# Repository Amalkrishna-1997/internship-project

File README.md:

# internship-project
dual smps ciruit controlled by esp32 with 3rd power sourse as a battery
smps control these 2 smps and battery controlled relay circuit

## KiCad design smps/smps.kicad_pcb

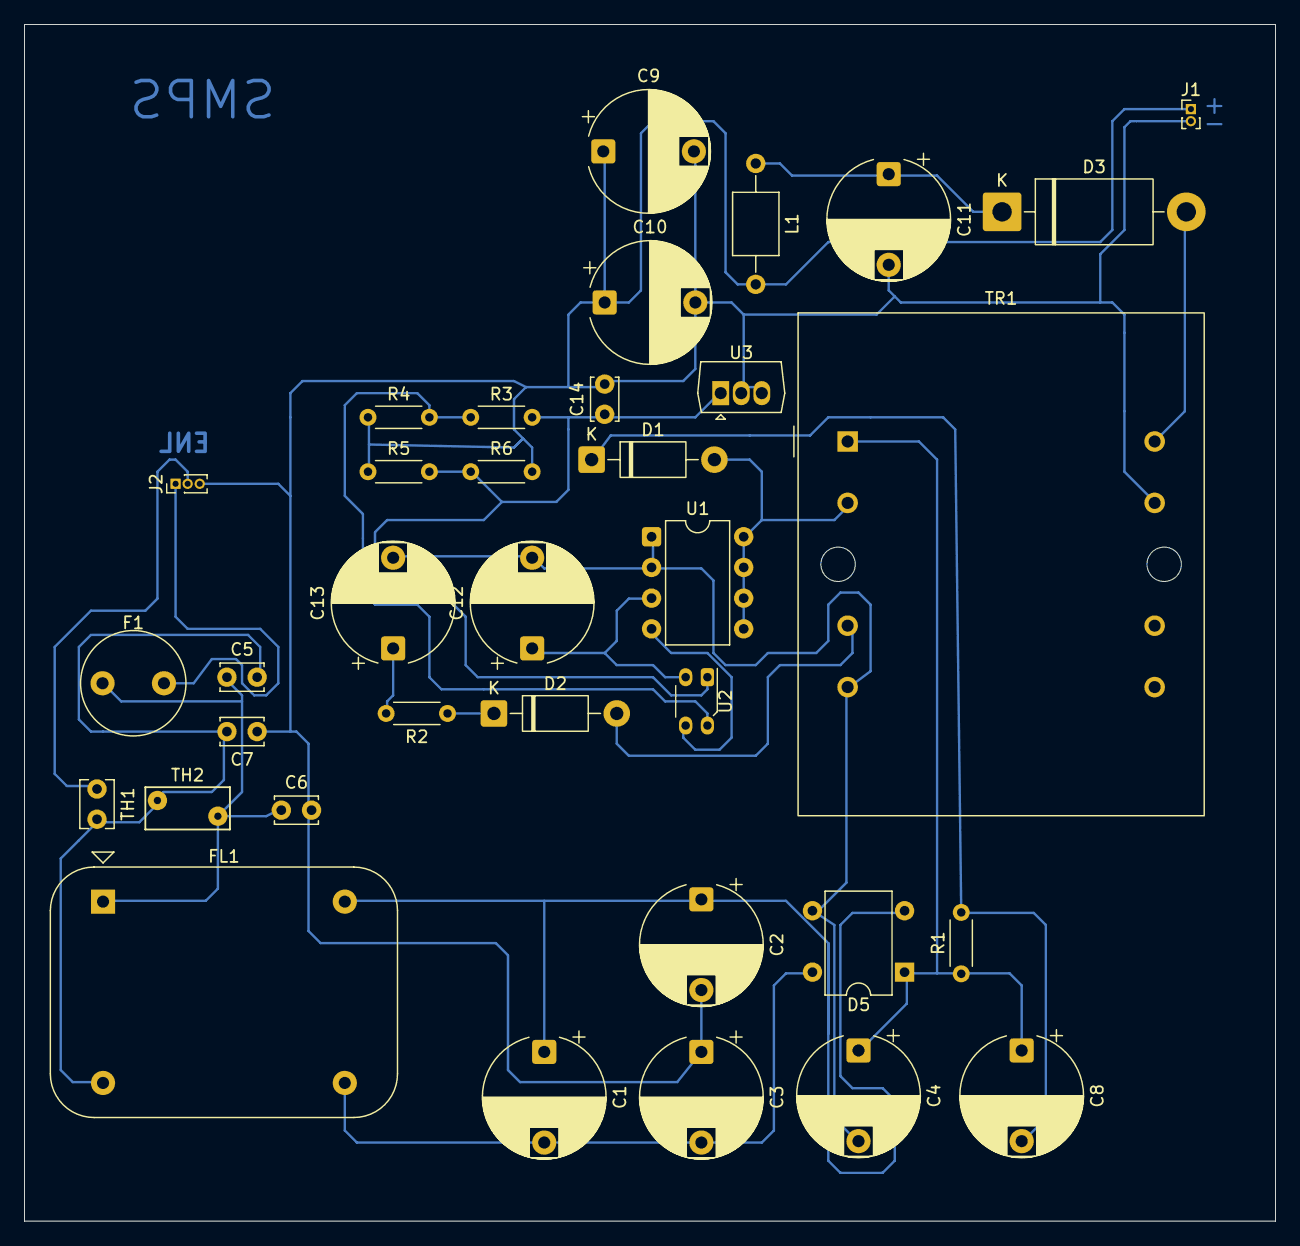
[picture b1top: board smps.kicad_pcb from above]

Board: 2 copper layers, 103.5 x 99.0 mm, 35 parts (0 on the bottom side), 21 nets, no tracks yet.

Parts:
C1, C2, C3, C8, C10, C11: C_Small; CP_Radial_D10.0mm_P7.50mm
C4, C9, C13: C_Polarized_US; CP_Radial_D10.0mm_P7.50mm
C5, C6, C7: C_Small; C_Disc_D3.4mm_W2.1mm_P2.50mm
C12: C; CP_Radial_D10.0mm_P7.50mm
C14: C; C_Disc_D3.4mm_W2.1mm_P2.50mm
D1, D2: 1N4936; D_DO-41_SOD81_P10.16mm_Horizontal
D3: 1N5822; D_DO-201AD_P15.24mm_Horizontal
D5: KBPC3501W; Diode_Bridge_DIP-4_W7.62mm_P5.08mm
F1: Fuse; Fuse_Littelfuse_372_D8.50mm
FL1: Filter_EMI_LL; Filter_FILTERCON_1FPxx
J1: Conn_01x02_Pin; PinHeader_1x02_P1.00mm_Vertical
J2: Conn_01x03_Pin; PinHeader_1x03_P1.00mm_Vertical
L1: L; L_Axial_L5.0mm_D3.6mm_P10.00mm_Horizontal_Murata_BL01RN1A2A2
R1: R_Small; R_Axial_DIN0204_L3.6mm_D1.6mm_P5.08mm_Horizontal
R2, R3, R4, R5, R6: R_Small_US; R_Axial_DIN0204_L3.6mm_D1.6mm_P5.08mm_Horizontal
TH1: Thermistor_NTC; C_Disc_D3.8mm_W2.6mm_P2.50mm
TH2: Thermistor_NTC; RV_Disc_D7mm_W3.5mm_P5mm
TR1: Triad_VPP16-310; Transformer_Triad_VPP16-310
U1: VIPer22AS; DIP-8_W7.62mm
U2: GP2S700HCP; Everlight_ITR8307F43
U3: TL431D; NEC_Molded_7x4x9mm

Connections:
Earth: C2.2, C3.1, C6.2, C7.1, C9.2, C10.2, C11.2, C14.2, J1.2, J2.3, R6.2, TR1.9, U3.2 (A), U3.3 (A)
unnamed: C1.1, C2.1, D5.2, FL1.2
unnamed: C1.2, C3.2, D5.4, FL1.4
unnamed: C5.1, C6.1, F1.1, FL1.1, TH2.1
unnamed: C5.2, C7.2, FL1.3, TH1.2, TH2.2
unnamed: C13.1, R2.2
unnamed: D1.2 (A), TR1.3, U1.5 (D), U1.6 (D), U1.7 (D), U1.8 (D)
unnamed: C8.2, D1.1 (K), R1.2
unnamed: D2.2 (A), TR1.4
unnamed: D2.1 (K), R2.1
unnamed: D3.2 (A), TR1.7
unnamed: C11.1, D3.1 (K), L1.1
unnamed: C4.1, C8.1, D5.1 (+), R1.1, TR1.1
unnamed: C4.2, C12.2, C13.2, D5.3 (-), TR1.6, U1.1 (S), U1.2 (S)
unnamed: C9.1, C10.1, J1.1, L1.2, R4.1, R5.1
unnamed: F1.2, J2.1
unnamed: J2.2, TH1.1
unnamed: R3.1, R4.2, U2.2
unnamed: C12.1, U1.3 (FB), U2.3 (K)
unnamed: U1.4 (VDD), U2.4 (A)
unnamed: C14.1, R3.2, R5.2, R6.1, U2.1, U3.1 (K)

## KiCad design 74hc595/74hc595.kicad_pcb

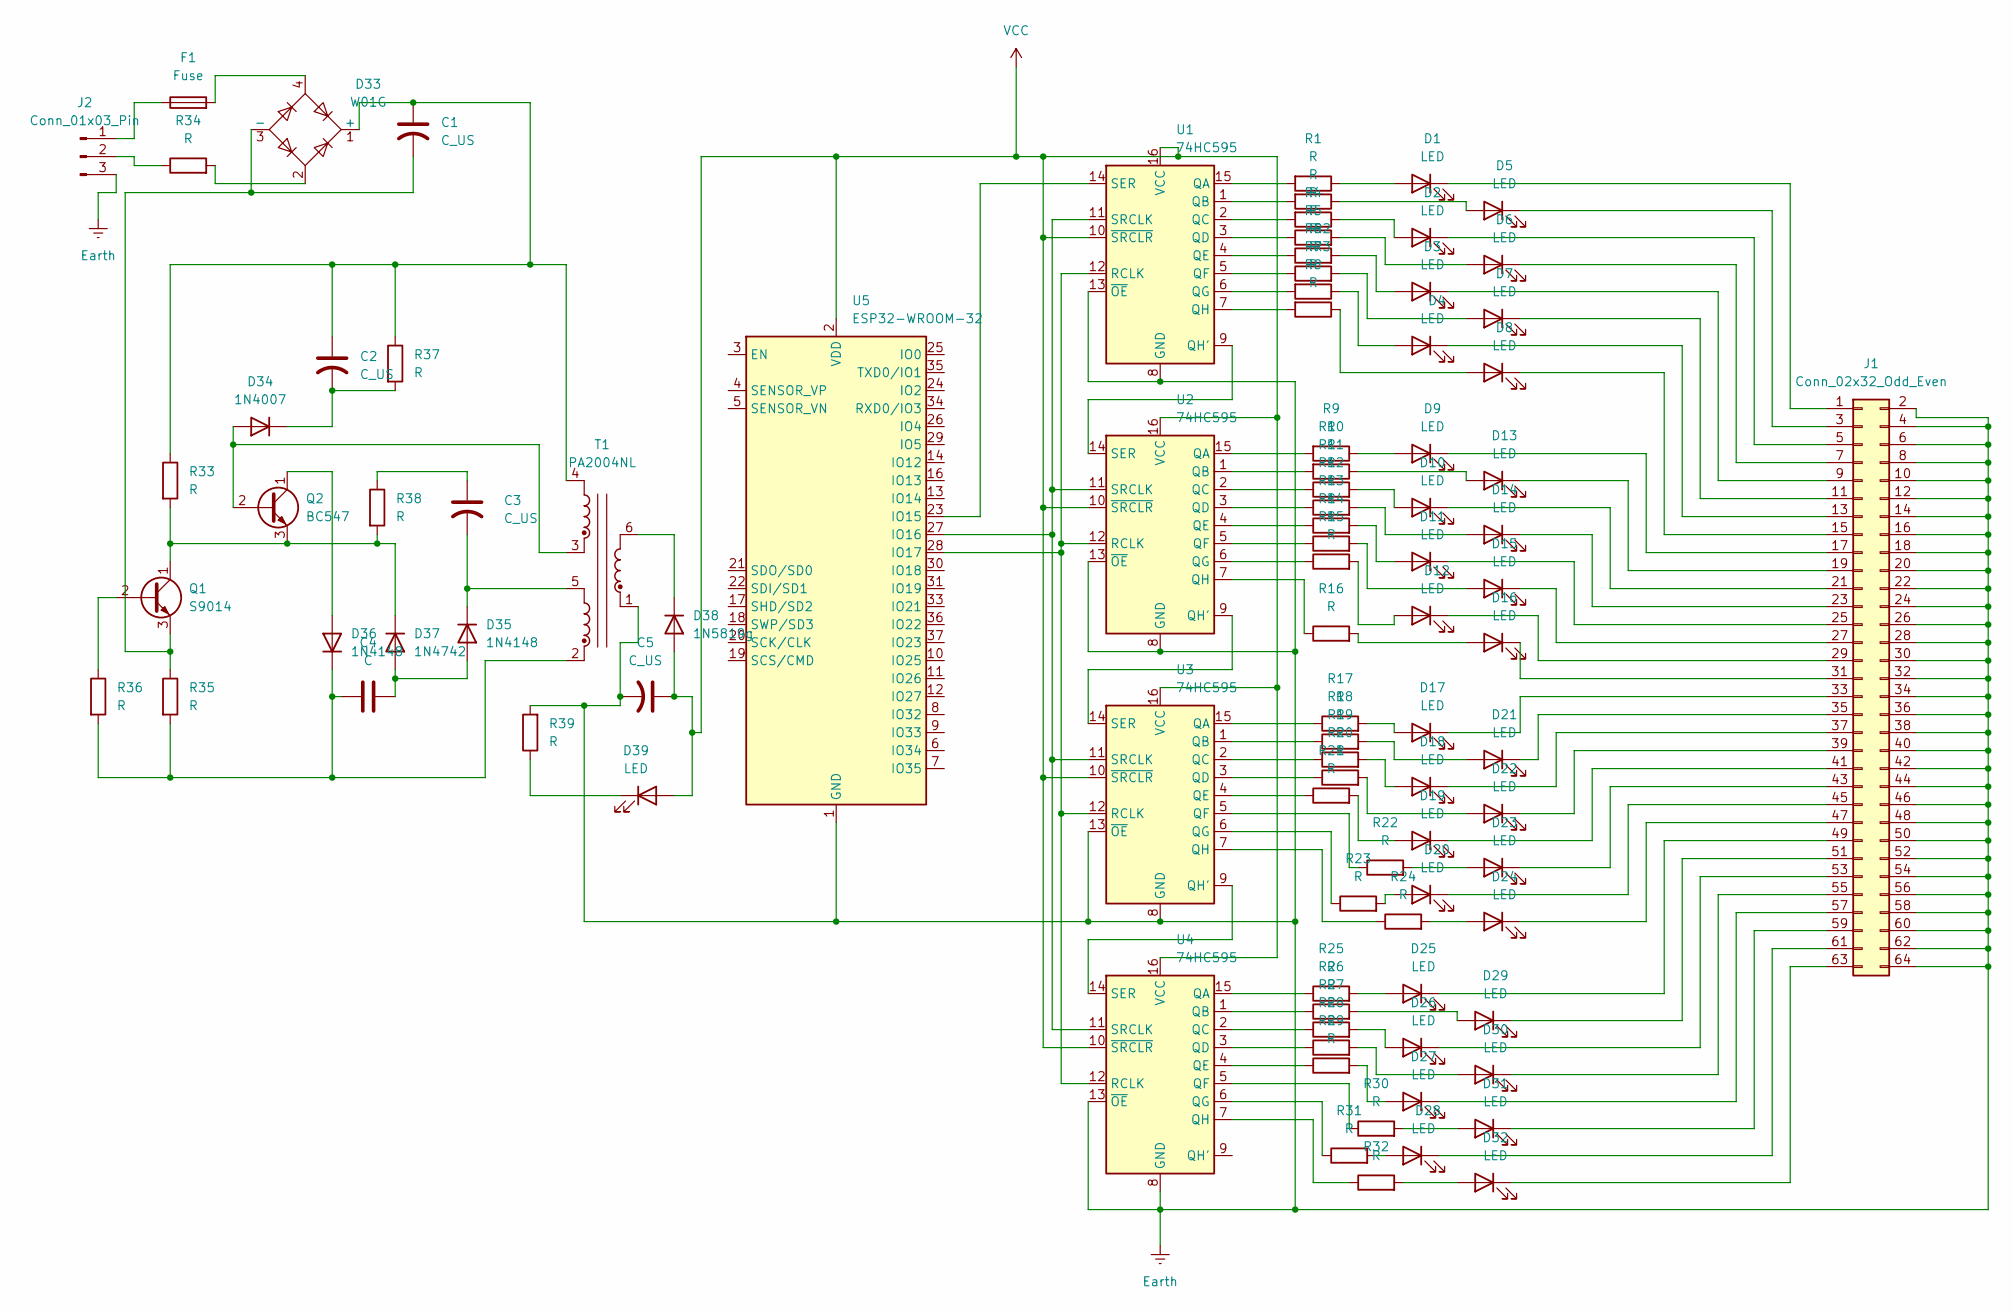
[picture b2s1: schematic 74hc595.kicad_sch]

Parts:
C1: C_US; CP_Radial_D12.5mm_P5.00mm
C2, C3: C_US; CP_Radial_D10.0mm_P5.00mm
C4: C; CP_Radial_D10.0mm_P5.00mm
C5: C_US; CP_Radial_D8.0mm_P3.80mm
D1, D2, D3, D4, D5, D6, D7, D8, D9, D10, D11, D12, D13, D14, D15, D16, D17, D18, D19, D20, D21, D22, D23, D24, D25, D26, D27, D28, D29, D30, D31, D32, D39: LED; LED_D4.0mm
D33: W01G; Diode_Bridge_Round_D9.8mm
D34: 1N4007; D_DO-41_SOD81_P10.16mm_Horizontal
D35, D36: 1N4148; D_DO-35_SOD27_P7.62mm_Horizontal
D37: 1N4742; D_DO-35_SOD27_P7.62mm_Horizontal
D38: 1N5819g; D_DO-41_SOD81_P10.16mm_Horizontal
F1: Fuse; Fuse_Bourns_MF-RG300
J1: Conn_02x32_Odd_Even; PinHeader_2x32_P1.27mm_Vertical
J2: Conn_01x03_Pin; Stocko_MKS_1653-6-0-303_1x3_P2.50mm_Vertical
Q1: S9014; TO-92_Inline
Q2: BC547; TO-92_Inline
R1, R2, R3, R4, R5, R6, R7, R8, R9, R10, R11, R12, R13, R14, R15, R16, R17, R18, R19, R20, R21, R22, R23, R24, R25, R26, R27, R28, R29, R30, R31, R32, R33, R34, R35, R36, R37, R38, R39: R; R_Axial_DIN0207_L6.3mm_D2.5mm_P10.16mm_Horizontal
T1: PA2004NL; Transformer_CHK_EI30-2VA_1xSec
U1, U2, U3, U4: 74HC595; DIP-16_W7.62mm
U5: ESP32-WROOM-32; ESP32-C3-DevKitM-1

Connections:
Earth: C5.2, J1.2, J1.4, J1.6, J1.8, J1.10, J1.12, J1.14, J1.16, J1.18, J1.20, J1.22, J1.24, J1.26, J1.28, J1.30, J1.32, J1.34, J1.36, J1.38, J1.40, J1.42, J1.44, J1.46, J1.48, J1.50, J1.52, J1.54, J1.56, J1.58, J1.60, J1.62, J1.64, J2.3, R39.2, T1.1, U1.8 (GND), U1.13 (~OE), U2.8 (GND), U2.13 (~OE), U3.8 (GND), U3.13 (~OE), U4.8 (GND), U4.13 (~OE), U5.1 (GND), U5.15 (GND), U5.38 (GND), U5.39 (GND)
unnamed: C3.1, R38.1
unnamed: D1.2 (A), R1.1
unnamed: D1.1 (K), J1.1
unnamed: D2.2 (A), R3.1
unnamed: D2.1 (K), J1.5
unnamed: D3.2 (A), R5.2
unnamed: D3.1 (K), J1.9
unnamed: D4.2 (A), R7.1
unnamed: D4.1 (K), J1.13
unnamed: D5.2 (A), R2.1
unnamed: D5.1 (K), J1.3
unnamed: D6.2 (A), R4.2
unnamed: D6.1 (K), J1.7
unnamed: D7.2 (A), R6.2
unnamed: D7.1 (K), J1.11
unnamed: D8.2 (A), R8.1
unnamed: D8.1 (K), J1.15
unnamed: D9.2 (A), R9.1
unnamed: D9.1 (K), J1.17
unnamed: D10.2 (A), R11.2
unnamed: D10.1 (K), J1.21
unnamed: D11.2 (A), R13.2
unnamed: D11.1 (K), J1.25
unnamed: D12.2 (A), R15.2
unnamed: D12.1 (K), J1.29
unnamed: D13.2 (A), R10.1
unnamed: D13.1 (K), J1.19
unnamed: D14.2 (A), R12.2
unnamed: D14.1 (K), J1.23
unnamed: D15.2 (A), R14.2
unnamed: D15.1 (K), J1.27
unnamed: D16.2 (A), R16.2
unnamed: D16.1 (K), J1.31
unnamed: D17.2 (A), R17.2
unnamed: D17.1 (K), J1.33
unnamed: D18.2 (A), R19.2
unnamed: D18.1 (K), J1.37
unnamed: D19.2 (A), R21.2
unnamed: D19.1 (K), J1.41
unnamed: D20.2 (A), R23.2
unnamed: D20.1 (K), J1.45
unnamed: D21.2 (A), R18.2
unnamed: D21.1 (K), J1.35
unnamed: D22.2 (A), R20.2
unnamed: D22.1 (K), J1.39
unnamed: D23.2 (A), R22.2
unnamed: D23.1 (K), J1.43
unnamed: D24.2 (A), R24.2
unnamed: D24.1 (K), J1.47
unnamed: D25.2 (A), R25.2
unnamed: D25.1 (K), J1.49
unnamed: D26.2 (A), R27.2
unnamed: D26.1 (K), J1.53
unnamed: D27.2 (A), R29.2
unnamed: D27.1 (K), J1.57
unnamed: D28.2 (A), R31.2
unnamed: D28.1 (K), J1.61
unnamed: D29.2 (A), R26.2
unnamed: D29.1 (K), J1.51
unnamed: D30.2 (A), R28.2
unnamed: D30.1 (K), J1.55
unnamed: D31.2 (A), R30.2
unnamed: D31.1 (K), J1.59
unnamed: D32.2 (A), R32.2
unnamed: D32.1 (K), J1.63
unnamed: C1.1, C2.1, D33.1 (+), R33.1, R37.1, T1.4
unnamed: C1.2, D33.3 (-), Q1.3 (E), R35.1
unnamed: D33.2, R34.2
unnamed: D33.4, F1.2
unnamed: D34.2 (A), Q2.2 (B), T1.3
unnamed: C2.2, D34.1 (K), R37.2
unnamed: C4.2, D35.2 (A), D37.2 (A)
unnamed: C3.2, D35.1 (K), T1.5
unnamed: D36.2 (A), Q2.1 (C)
unnamed: C4.1, D36.1 (K), R35.2, R36.2, T1.2
unnamed: D37.1 (K), Q1.1 (C), Q2.3 (E), R33.2, R38.2
unnamed: D38.1 (K), T1.6
unnamed: D39.1 (K), R39.1
unnamed: F1.1, J2.1
unnamed: J2.2, R34.1
unnamed: Q1.2 (B), R36.1
unnamed: R1.2, U1.15 (QA)
unnamed: R2.2, U1.1 (QB)
unnamed: R3.2, U1.2 (QC)
unnamed: R4.1, U1.3 (QD)
unnamed: R5.1, U1.4 (QE)
unnamed: R6.1, U1.5 (QF)
unnamed: R7.2, U1.6 (QG)
unnamed: U1.9 (QH'), U2.14 (SER)
unnamed: R8.2, U1.7 (QH)
unnamed: U1.12 (RCLK), U2.12 (RCLK), U3.12 (RCLK), U4.12 (RCLK), U5.28 (IO17)
unnamed: U1.14 (SER), U5.23 (IO15)
unnamed: U1.11 (SRCLK), U2.11 (SRCLK), U3.11 (SRCLK), U4.11 (SRCLK), U5.27 (IO16)
unnamed: R9.2, U2.15 (QA)
unnamed: R10.2, U2.1 (QB)
unnamed: R11.1, U2.2 (QC)
unnamed: R12.1, U2.3 (QD)
unnamed: R13.1, U2.4 (QE)
unnamed: R14.1, U2.5 (QF)
unnamed: R15.1, U2.6 (QG)
unnamed: U2.9 (QH'), U3.14 (SER)
unnamed: R16.1, U2.7 (QH)
unnamed: R17.1, U3.15 (QA)
unnamed: R18.1, U3.1 (QB)
unnamed: R19.1, U3.2 (QC)
unnamed: R20.1, U3.3 (QD)
unnamed: R21.1, U3.4 (QE)
unnamed: R22.1, U3.5 (QF)
unnamed: R23.1, U3.6 (QG)
unnamed: U3.9 (QH'), U4.14 (SER)
unnamed: R24.1, U3.7 (QH)
unnamed: R25.1, U4.15 (QA)
unnamed: R26.1, U4.1 (QB)
unnamed: R27.1, U4.2 (QC)
unnamed: R28.1, U4.3 (QD)
unnamed: R29.1, U4.4 (QE)
unnamed: R30.1, U4.5 (QF)
unnamed: R31.1, U4.6 (QG)
unnamed: R32.1, U4.7 (QH)
VCC: C5.1, D38.2 (A), D39.2 (A), U1.10 (~SRCLR), U1.16 (VCC), U2.10 (~SRCLR), U2.16 (VCC), U3.10 (~SRCLR), U3.16 (VCC), U4.10 (~SRCLR), U4.16 (VCC), U5.2 (VDD)

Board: 2 copper layers, 94 parts (0 on the bottom side), 121 nets, no tracks yet.

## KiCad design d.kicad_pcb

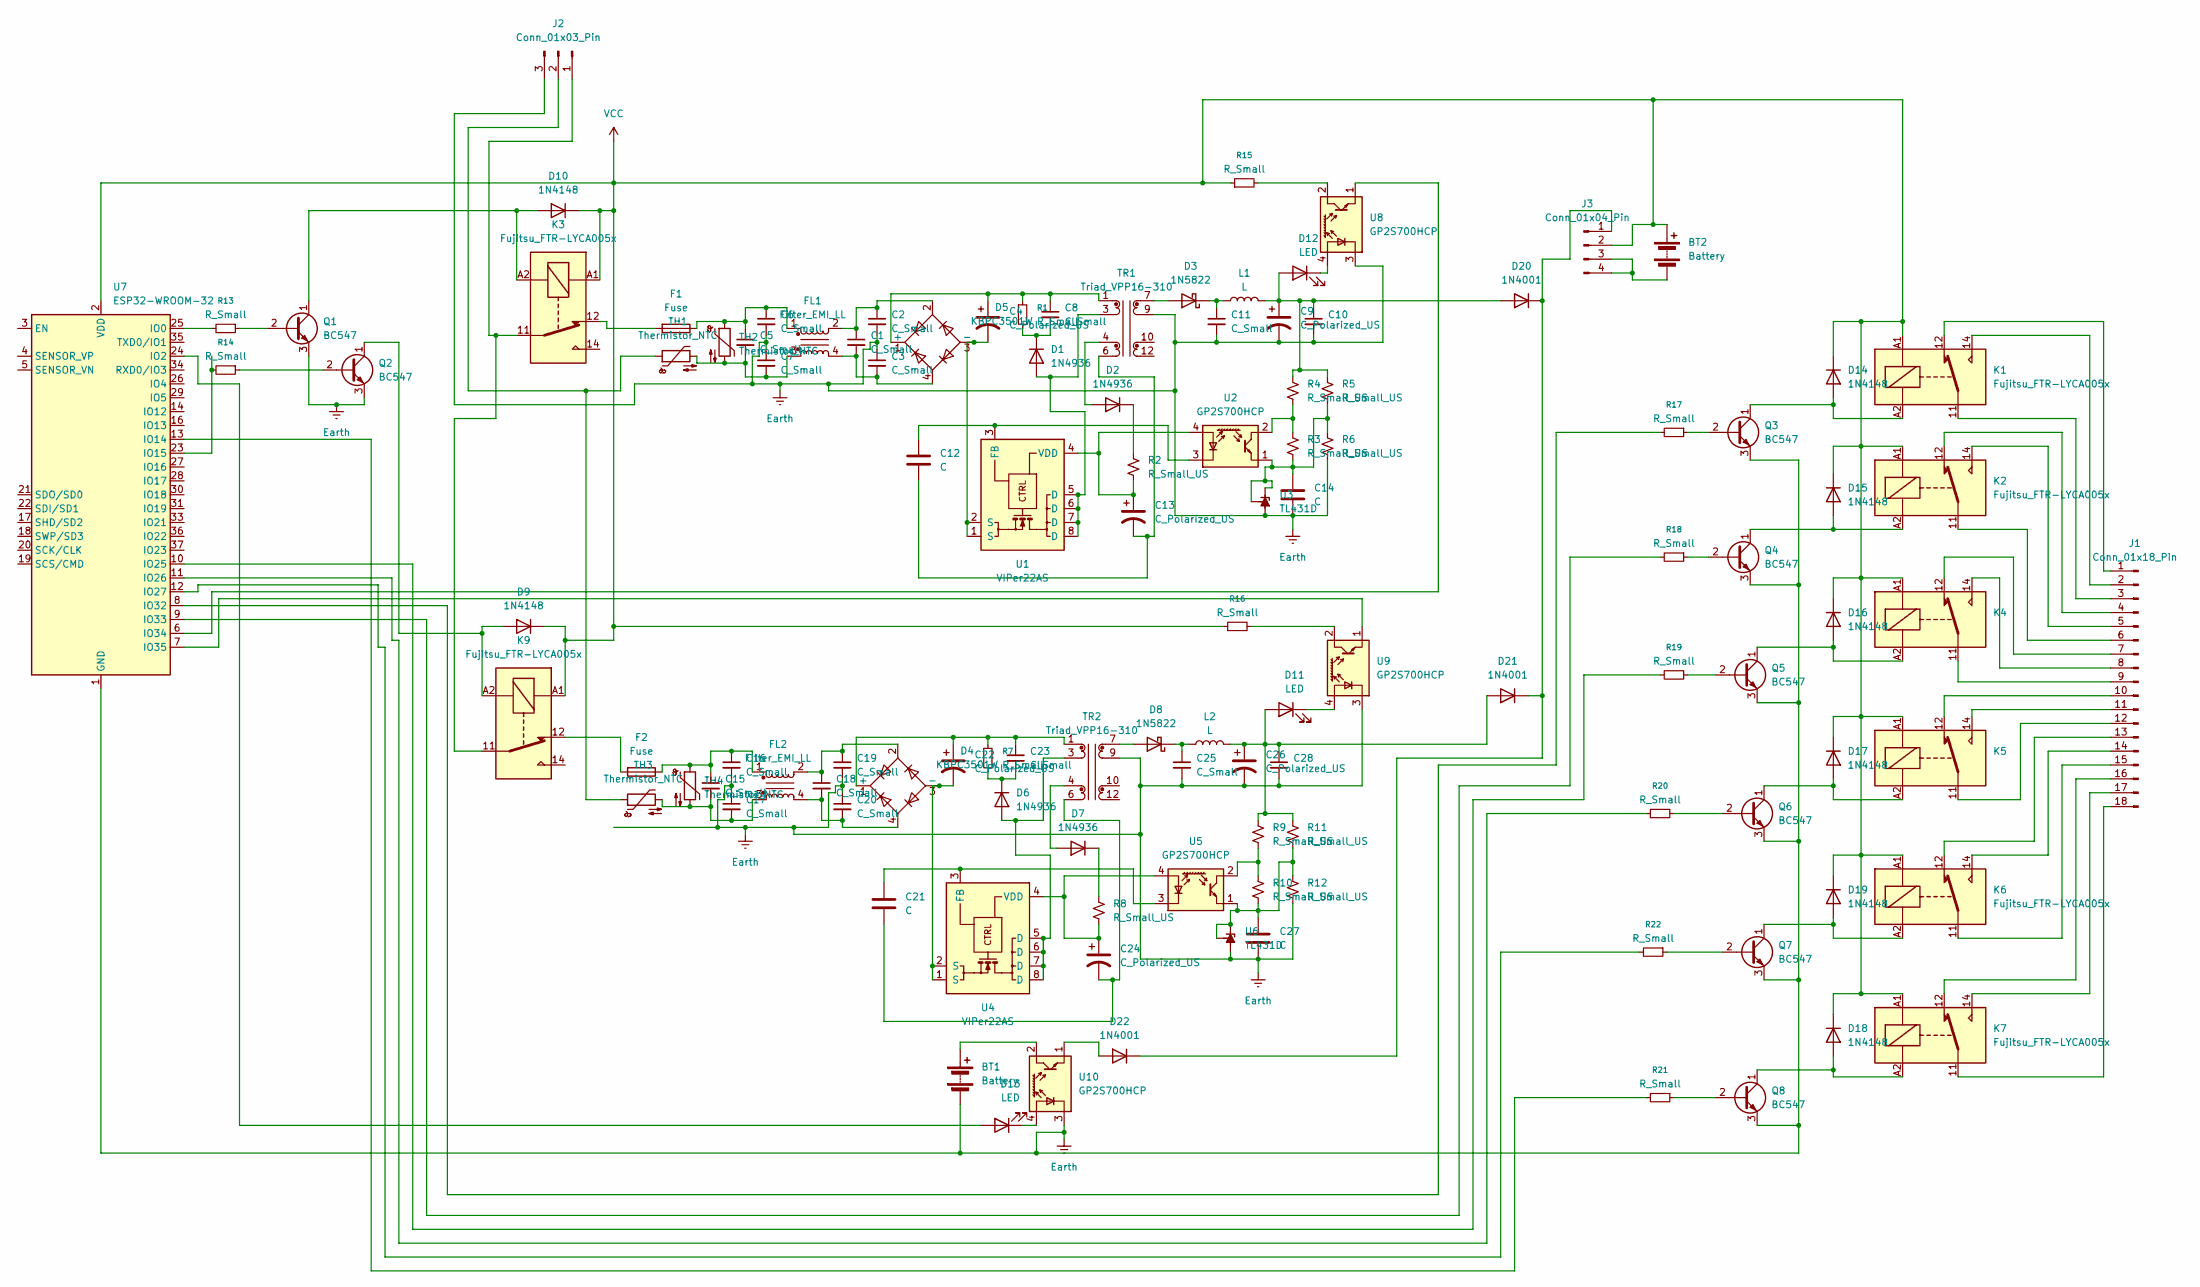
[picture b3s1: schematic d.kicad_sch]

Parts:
BT1: Battery; BatteryHolder_Keystone_2466_1xAAA
BT2: Battery; BatteryHolder_MYOUNG_BS-07-A1BJ001_CR2032
C1, C2, C3, C8, C10, C11, C18, C19, C20, C23, C25, C28: C_Small; CP_Radial_D10.0mm_P7.50mm
C4, C9, C13, C22, C24, C26: C_Polarized_US; CP_Radial_D10.0mm_P7.50mm
C5, C6, C7, C15, C16, C17: C_Small; C_Disc_D3.4mm_W2.1mm_P2.50mm
C12, C21: C; CP_Radial_D10.0mm_P7.50mm
C14, C27: C; C_Disc_D3.0mm_W2.0mm_P2.50mm
D1, D2, D6, D7: 1N4936; D_DO-41_SOD81_P10.16mm_Horizontal
D3, D8: 1N5822; D_DO-201AD_P15.24mm_Horizontal
D4, D5: KBPC3501W; Diode_Bridge_DIP-4_W7.62mm_P5.08mm
D9, D10, D14, D15, D16, D17, D18, D19: 1N4148; D_DO-35_SOD27_P7.62mm_Horizontal
D11, D12, D13: LED; LED_D5.0mm
D20, D21, D22: 1N4001; D_DO-41_SOD81_P10.16mm_Horizontal
F1, F2: Fuse; Fuse_Littelfuse_372_D8.50mm
FL1, FL2: Filter_EMI_LL; Filter_FILTERCON_1FPxx
J1: Conn_01x18_Pin; PinHeader_1x18_P1.00mm_Vertical
J2: Conn_01x03_Pin; PinHeader_1x03_P1.00mm_Vertical
J3: Conn_01x04_Pin; PinHeader_1x04_P2.00mm_Vertical
K1, K2, K3, K4, K5, K6, K7, K9: Fujitsu_FTR-LYCA005x; Relay_SPDT_Finder_40.41
L1, L2: L; L_Axial_L5.0mm_D3.6mm_P10.00mm_Horizontal_Murata_BL01RN1A2A2
Q1, Q2, Q3, Q4, Q5, Q6, Q7, Q8: BC547; TO-92_Inline
R1, R7, R15, R16, R17, R18, R19, R20, R21, R22: R_Small; R_Axial_DIN0204_L3.6mm_D1.6mm_P5.08mm_Horizontal
R2, R3, R4, R5, R6, R8, R9, R10, R11, R12: R_Small_US; R_Axial_DIN0204_L3.6mm_D1.6mm_P5.08mm_Horizontal
R13, R14: R_Small; R_Axial_DIN0204_L3.6mm_D1.6mm_P7.62mm_Horizontal
TH1, TH3: Thermistor_NTC; C_Disc_D3.8mm_W2.6mm_P2.50mm
TH2, TH4: Thermistor_NTC; RV_Disc_D7mm_W3.5mm_P5mm
TR1, TR2: Triad_VPP16-310; Transformer_Triad_VPP16-310
U1, U4: VIPer22AS; DIP-8_W7.62mm
U2, U5, U8, U9, U10: GP2S700HCP; Everlight_ITR8307F43
U3, U6: TL431D; SIPAK_Vertical
U7: ESP32-WROOM-32; ESP32-C3-DevKitM-1

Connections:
Earth: BT1.2 (-), C2.2, C3.1, C6.2, C7.1, C9.2, C10.2, C11.2, C14.2, C16.2, C17.1, C19.2, C20.1, C25.2, C26.2, C27.2, C28.2, J2.3, Q1.3 (E), Q2.3 (E), Q3.3 (E), Q4.3 (E), Q5.3 (E), Q6.3 (E), Q7.3 (E), Q8.3 (E), R6.2, R12.2, TR1.9, TR2.9, U3.2 (A), U3.3 (A), U3.6 (A), U3.7 (A), U6.2 (A), U6.3 (A), U6.6 (A), U6.7 (A), U7.1 (GND), U7.15 (GND), U7.38 (GND), U7.39 (GND), U8.3 (K), U9.3 (K), U10.3 (K)
unnamed: BT1.1 (+), U10.2
unnamed: BT2.2 (-), J3.3, J3.4
unnamed: C1.1, C2.1, D5.2, FL1.2
unnamed: C1.2, C3.2, D5.4, FL1.4
unnamed: C5.1, C6.1, F1.1, FL1.1, TH2.1
unnamed: C5.2, C7.2, FL1.3, TH1.2, TH2.2
unnamed: C12.2, C13.2, TR1.6
unnamed: C15.1, C16.1, F2.1, FL2.1, TH4.1
unnamed: C15.2, C17.2, FL2.3, TH3.2, TH4.2
unnamed: C18.1, C19.1, D4.2, FL2.2
unnamed: C18.2, C20.2, D4.4, FL2.4
unnamed: C21.2, C24.2, TR2.6
unnamed: D1.2 (A), TR1.3, U1.5 (D), U1.6 (D), U1.7 (D), U1.8 (D)
unnamed: C8.2, D1.1 (K), R1.2
unnamed: D2.2 (A), TR1.4
unnamed: D2.1 (K), R2.1
unnamed: D3.2 (A), TR1.7
unnamed: C11.1, D3.1 (K), L1.1
unnamed: C22.1, C23.1, D4.1 (+), R7.1, TR2.1
unnamed: C22.2, D4.3 (-), U4.1 (S), U4.2 (S)
unnamed: C4.1, C8.1, D5.1 (+), R1.1, TR1.1
unnamed: C4.2, D5.3 (-), U1.1 (S), U1.2 (S)
unnamed: D6.2 (A), TR2.3, U4.5 (D), U4.6 (D), U4.7 (D), U4.8 (D)
unnamed: C23.2, D6.1 (K), R7.2
unnamed: D7.2 (A), TR2.4
unnamed: D7.1 (K), R8.1
unnamed: D8.2 (A), TR2.7
unnamed: C25.1, D8.1 (K), L2.1
unnamed: D9.2 (A), K9.A2, Q2.1 (C)
unnamed: D10.2 (A), K3.A2, Q1.1 (C)
unnamed: C26.1, C28.1, D11.2 (A), D21.2 (A), L2.2, R9.1, R11.1
unnamed: D11.1 (K), U9.4 (A)
unnamed: C9.1, C10.1, D12.2 (A), D20.2 (A), L1.2, R4.1, R5.1
unnamed: D12.1 (K), U8.4 (A)
unnamed: D13.2 (A), U7.24 (IO2)
unnamed: D13.1 (K), U10.4 (A)
unnamed: D14.2 (A), K1.A2, Q3.1 (C)
unnamed: D15.2 (A), K2.A2, Q4.1 (C)
unnamed: D16.2 (A), K4.A2, Q5.1 (C)
unnamed: D17.2 (A), K5.A2, Q6.1 (C)
unnamed: D18.2 (A), K7.A2, Q8.1 (C)
unnamed: D19.2 (A), K6.A2, Q7.1 (C)
unnamed: D20.1 (K), D21.1 (K), D22.1 (K), J3.1
unnamed: D22.2 (A), U10.1
unnamed: F1.2, K3.12
unnamed: F2.2, K9.12
unnamed: J1.1, K1.12
unnamed: J1.2, K1.14
unnamed: J1.3, K1.11
unnamed: J1.4, K2.12
unnamed: J1.5, K2.14
unnamed: J1.6, K2.11
unnamed: J1.7, K4.12
unnamed: J1.8, K4.14
unnamed: J1.9, K4.11
unnamed: J1.10, K5.12
unnamed: J1.11, K5.14
unnamed: J1.12, K5.11
unnamed: J1.13, K6.12
unnamed: J1.14, K6.14
unnamed: J1.15, K6.11
unnamed: J1.16, K7.12
unnamed: J1.17, K7.14
unnamed: J1.18, K7.11
unnamed: J2.1, K3.11, K9.11
unnamed: J2.2, TH1.1, TH3.1
unnamed: Q1.2 (B), R13.1
unnamed: Q2.2 (B), R14.1
unnamed: Q3.2 (B), R17.1
unnamed: Q4.2 (B), R18.1
unnamed: Q5.2 (B), R19.1
unnamed: Q6.2 (B), R20.1
unnamed: Q7.2 (B), R22.1
unnamed: Q8.2 (B), R21.1
unnamed: R3.1, R4.2, U2.2
unnamed: R9.2, R10.1, U5.2
unnamed: R15.2, U8.2
unnamed: R16.2, U9.2
unnamed: C12.1, U1.3 (FB), U2.3 (K)
unnamed: C13.1, R2.2, U1.4 (VDD), U2.4 (A)
unnamed: C14.1, R3.2, R5.2, R6.1, U2.1, U3.1 (K), U3.8 (REF)
unnamed: C21.1, U4.3 (FB), U5.3 (K)
unnamed: C24.1, R8.2, U4.4 (VDD), U5.4 (A)
unnamed: C27.1, R10.2, R11.2, R12.1, U5.1, U6.1 (K), U6.8 (REF)
unnamed: R13.2, U7.25 (IO0)
unnamed: R21.2, U7.13 (IO14)
unnamed: R14.2, U7.23 (IO15)
unnamed: R19.2, U7.10 (IO25)
unnamed: R20.2, U7.11 (IO26)
unnamed: R22.2, U7.12 (IO27)
unnamed: R17.2, U7.8 (IO32)
unnamed: R18.2, U7.9 (IO33)
unnamed: U7.6 (IO34), U8.1
unnamed: U7.7 (IO35), U9.1
VCC: BT2.1 (+), D9.1 (K), D10.1 (K), D14.1 (K), D15.1 (K), D16.1 (K), D17.1 (K), D18.1 (K), D19.1 (K), J3.2, K1.A1, K2.A1, K3.A1, K4.A1, K5.A1, K6.A1, K7.A1, K9.A1, R15.1, R16.1, U7.2 (VDD)

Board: 2 copper layers, 115 parts (0 on the bottom side), 96 nets, no tracks yet.
